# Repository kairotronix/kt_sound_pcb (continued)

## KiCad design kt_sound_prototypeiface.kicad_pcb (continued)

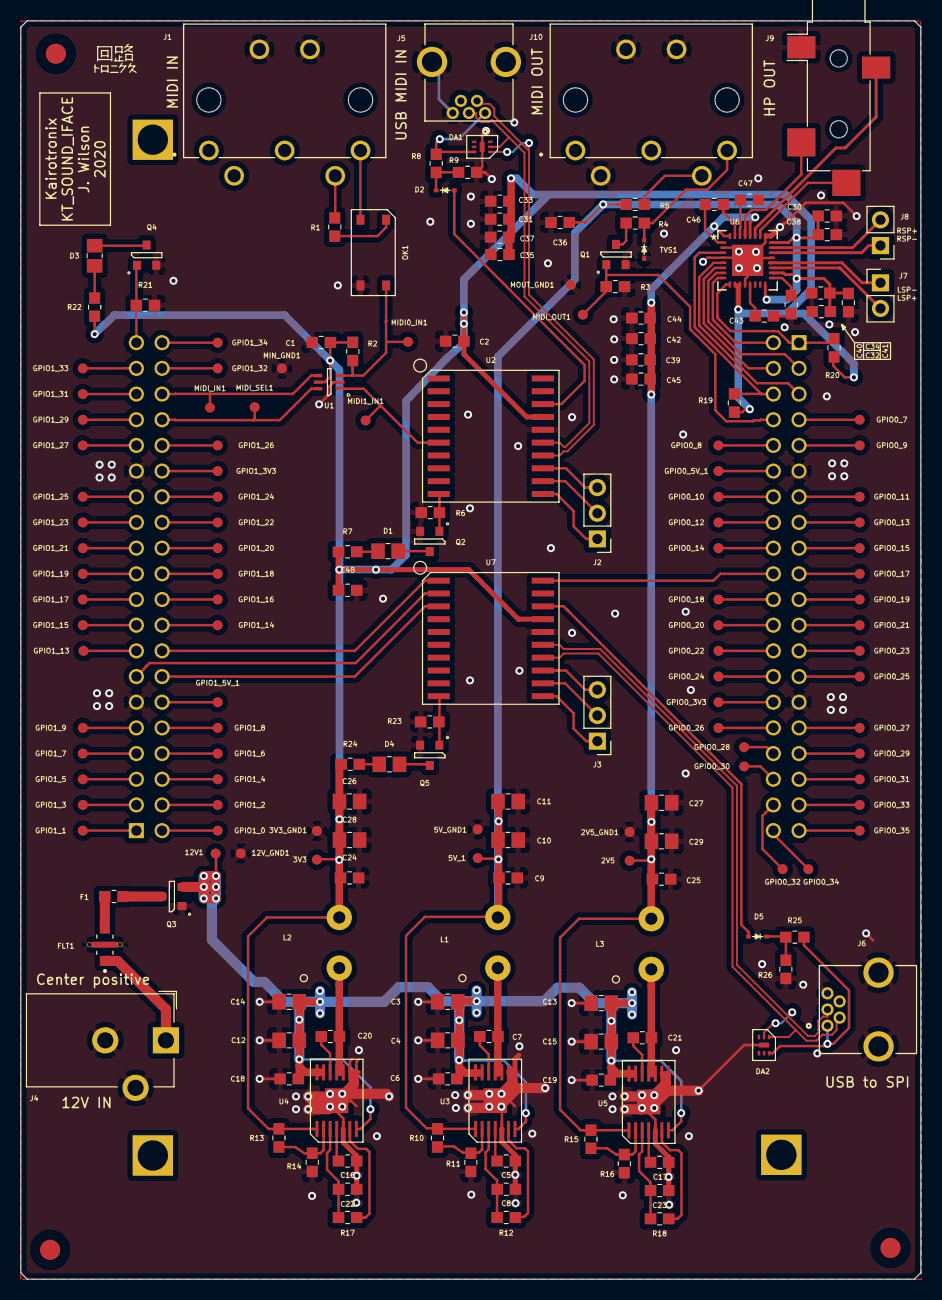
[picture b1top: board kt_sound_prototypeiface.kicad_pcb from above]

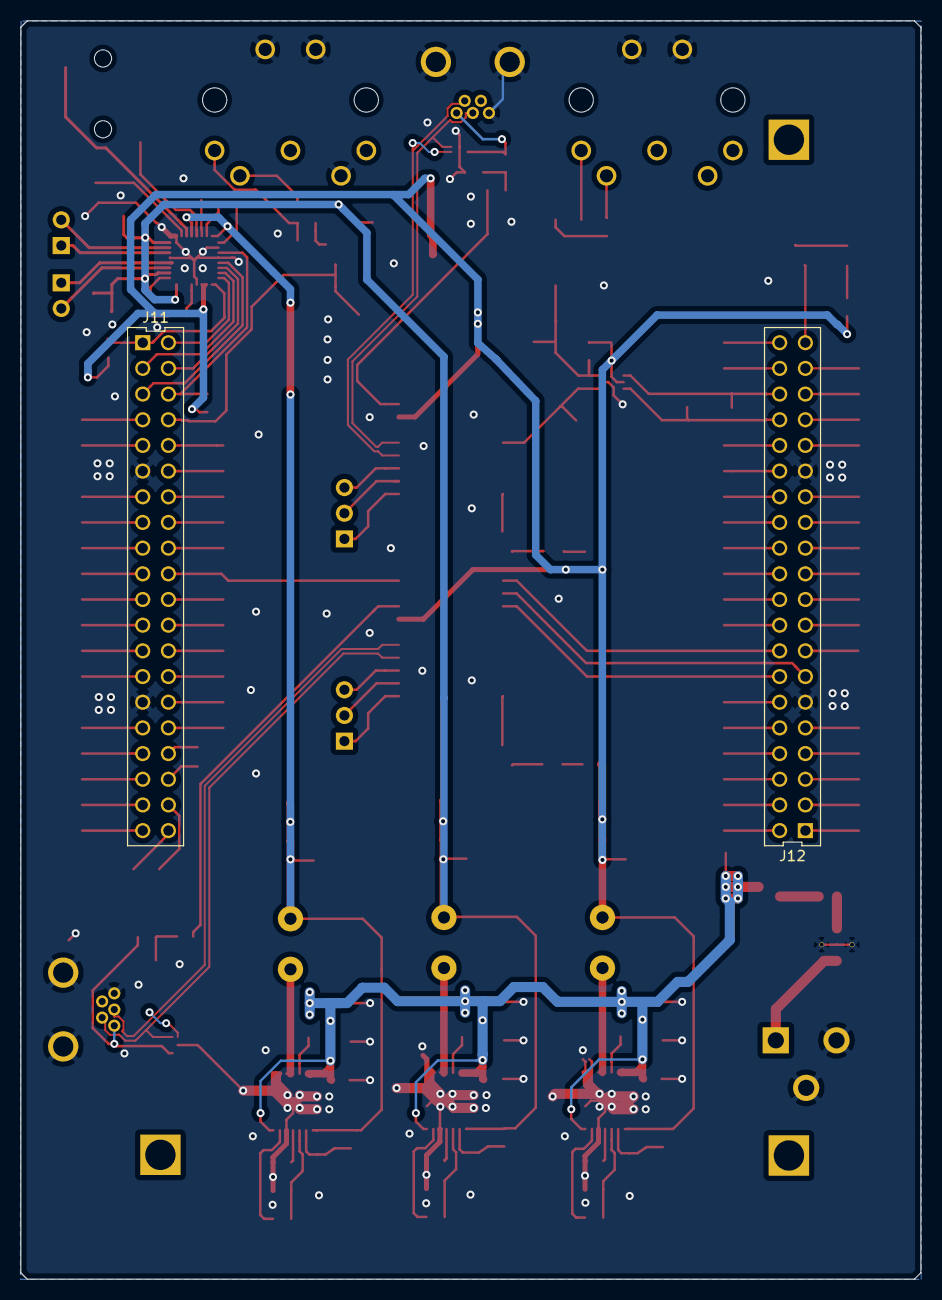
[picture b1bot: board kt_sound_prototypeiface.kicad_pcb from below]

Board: 2 copper layers, 89.0 x 124.5 mm, 192 parts (2 on the bottom side), 146 nets.

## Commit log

2020-05-03 Initial upload
    Initial upload of project PCB files. Contains schematics and PCB file.
2020-05-03 A little bit of cleanup pre-verification of the schematic.
2020-05-03 Noticed issue in POWER_MGMT.sch. Connected enable to VCC, routed changes accordingly.
2020-05-03 Adding some more thermal vias on power circuitry.
    Moved some reference designators to a more logical location
    TODO:
    *Finish verification of audio amp
    *Finish verification of USB to MIDI/SPI circuits
    *Confirm footprints against datasheets for active components and unique passives.
2020-05-03 Added comments in USB schematics.
    Put SPI on SERCOM0 in USB_SPI.sch, in routing realized it would be easier to split SPI between GPIO. This may be an issue in the future or may limit maximum SPI frequency.
2020-05-03 Updated schematic. DVDD was set to 5V but it was meant to be set to 3V3, likewise VDD was set to 3V3 but was meant to be set to 5V.
    Updated PCB for schematic changes.
    Updated PCB to single sided construction (for SMT parts) by moving the diode arrays to the top. This may cause some issues with USB due to stray capacitance but things will likely be fine at USB full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
2020-05-03 Saved files and confirmed everything was OK one last time.
2020-05-04 Added fiducials to the PCB in 3 corners. Moved some silk to accommodate this.
2020-05-05 Using the DXF of the DE10-Nano devkit I ensured placement of critical components was adequate. Mounting holes were moved slightly to ensure proper alignment.
    One GND via was added near the I2S amplifier to ensure a stronger gnd connection.
2020-05-06 Updated SMT PCB footprints and updated PCB. Added surface mount device flag so they would be added to the pick and place file.
2020-05-19 Added files for fabrication. Added PDF of schematics. Fixed minor issue in PCB footprint and updated PCB accordingly. Added symbol cache so schematics can be viewed in kicad without having my persona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
